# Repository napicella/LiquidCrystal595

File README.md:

# LiquidCrystal595
Connect a 16x2 LCD with 3 instead of 6 pins.

Original Arduino libary from [rowansimms]<br />
https://bitbucket.org/rowansimms/arduino-lcd-3pin

# Installation
Copy LiquidCrystal595 folder to Arduino folder.<br />
Include it in your Adruino sketch.

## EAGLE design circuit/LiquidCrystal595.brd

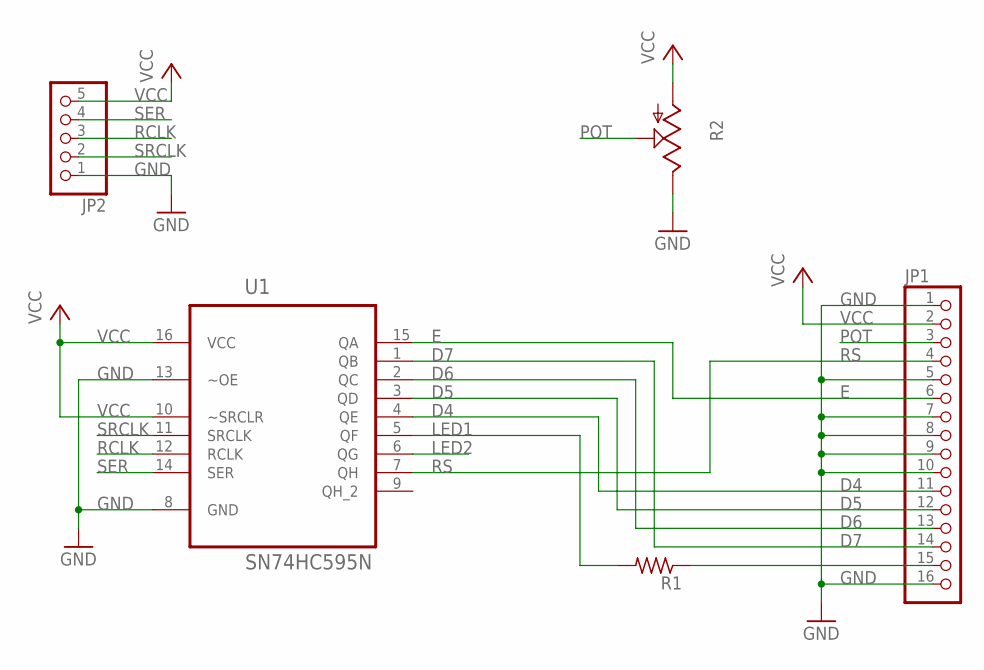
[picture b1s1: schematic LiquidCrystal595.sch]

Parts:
JP1: PINHD-1X16; 1X16
JP2: PINHD-1X5; 1X05
R1: R-US_0204/7; 0204/7
R2: TRIM_US-B25P; B25P
U1: SN74HC595N; DIP254P762X508-16

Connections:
D4: JP1.11, U1.4 (QE)
D5: JP1.12, U1.3 (QD)
D6: JP1.13, U1.2 (QC)
D7: JP1.14, U1.1 (QB)
E: JP1.6, U1.15 (QA)
GND: JP1.1, JP1.5, JP1.7, JP1.8, JP1.9, JP1.10, JP1.16, JP2.1, R2.E, U1.8 (GND), U1.13 (~OE)
LED1: R1.2, U1.5 (QF)
LED2: U1.6 (QG)
unnamed: JP1.15, R1.1
POT: JP1.3, R2.S
RCLK: JP2.3, U1.12 (RCLK)
RS: JP1.4, U1.7 (QH)
SER: JP2.4, U1.14 (SER)
SRCLK: JP2.2, U1.11 (SRCLK)
VCC: JP1.2, JP2.5, R2.A, U1.10 (~SRCLR), U1.16 (VCC)

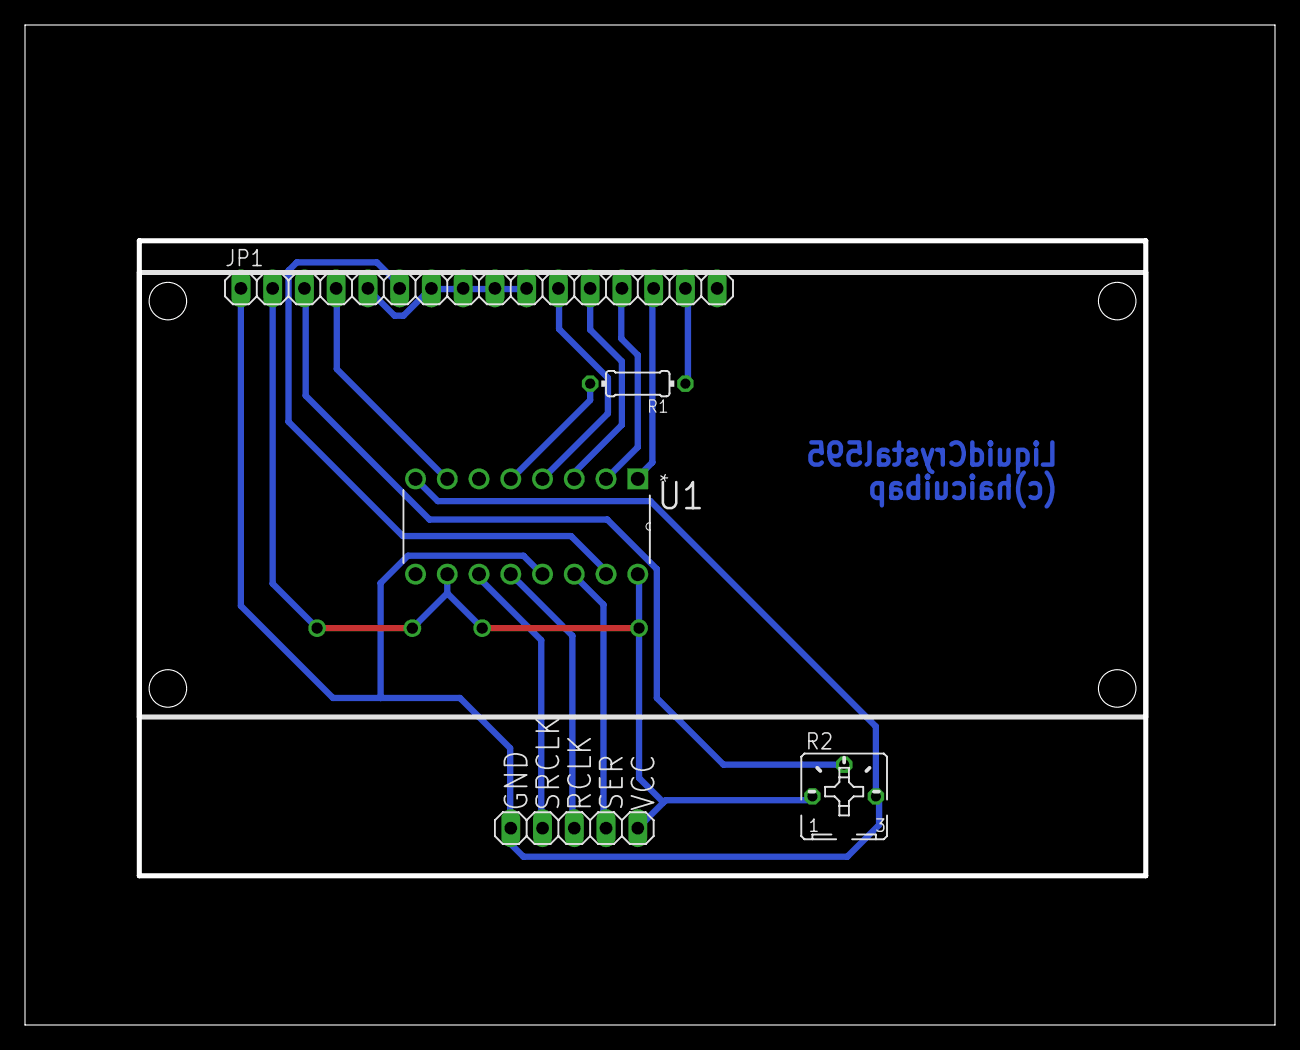
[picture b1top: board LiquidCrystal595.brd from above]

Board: 2 copper layers, 100.0 x 80.0 mm, 5 parts (0 on the bottom side), 14 nets.

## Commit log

2015-09-20 :lollipop: Added .gitattributes
2015-09-20 Create LICENSE
2015-09-20 daute
2020-04-25 Fix bug which cause the LCD to display only the first character
